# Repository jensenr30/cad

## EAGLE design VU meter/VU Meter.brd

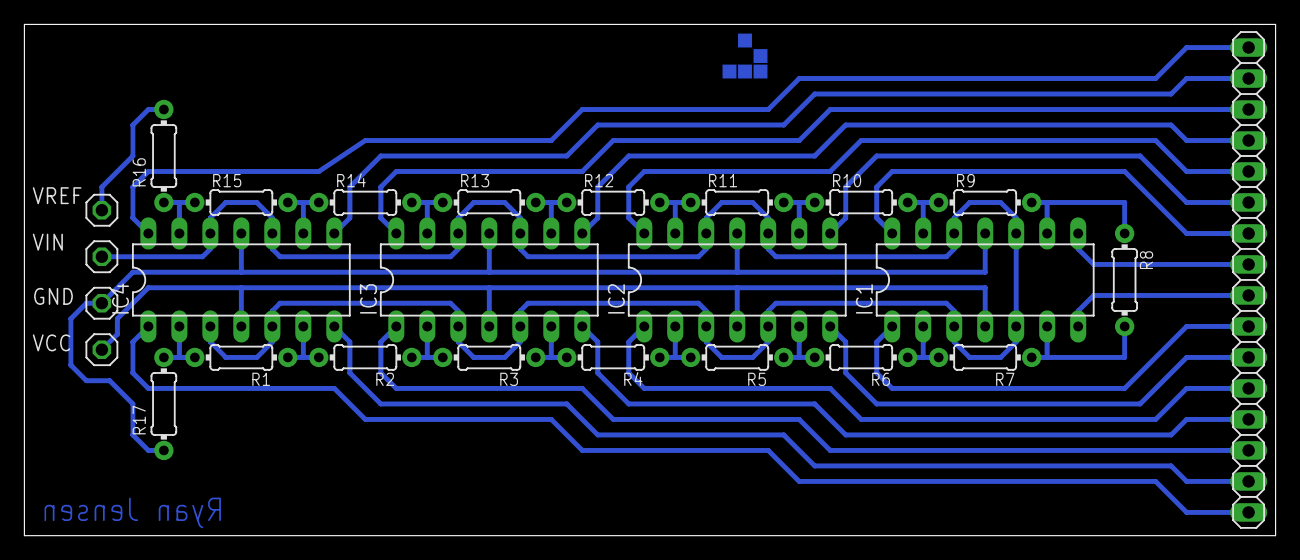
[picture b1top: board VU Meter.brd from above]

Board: 2 copper layers, 102.5 x 41.9 mm, 26 parts (0 on the bottom side), 36 nets.

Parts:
GND: 1X01
IC1, IC2, IC3, IC4: LM324N; DIL14
JP4: 1X16
R1, R2, R3, R4, R5, R6, R7, R8, R9, R10, R11, R12, R13, R14, R15, R16, R17: 10k; 0204/7
VCC: 1X01
VIN: 1X01
VREF: 1X01

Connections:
AGND: GND.1, IC1.11, IC2.11, IC3.11, IC4.11, R17.2
unnamed: IC4.9, R14.1, R15.2
unnamed: IC1.3, IC1.5, IC1.10, IC1.12, IC2.3, IC2.5, IC2.10, IC2.12, IC3.3, IC3.5, IC3.10, IC3.12, IC4.3, IC4.5, IC4.10, IC4.12, VIN.1
unnamed: IC3.13, R13.1, R14.2
unnamed: IC3.9, R12.1, R13.2
unnamed: IC2.13, R11.1, R12.2
unnamed: IC2.9, R10.1, R11.2
unnamed: IC1.13, R9.1, R10.2
unnamed: IC4.13, R15.1, R16.2
unnamed: IC4.2, R1.2, R17.1
unnamed: IC4.6, R1.1, R2.2
unnamed: IC3.2, R2.1, R3.2
unnamed: IC3.6, R3.1, R4.2
unnamed: IC2.2, R4.1, R5.2
unnamed: IC2.6, R5.1, R6.2
unnamed: IC1.2, R6.1, R7.2
unnamed: IC1.6, R7.1, R8.2
unnamed: IC1.9, R8.1, R9.2
unnamed: R16.1, VREF.1
unnamed: IC4.14, JP4.1
unnamed: IC4.8, JP4.2
unnamed: IC3.14, JP4.3
unnamed: IC3.8, JP4.4
unnamed: IC2.14, JP4.5
unnamed: IC2.8, JP4.6
unnamed: IC1.14, JP4.7
unnamed: IC1.8, JP4.8
unnamed: IC1.7, JP4.9
unnamed: IC1.1, JP4.10
unnamed: IC2.7, JP4.11
unnamed: IC4.1, JP4.16
unnamed: IC4.7, JP4.15
unnamed: IC3.1, JP4.14
unnamed: IC3.7, JP4.13
unnamed: IC2.1, JP4.12
V+: IC1.4, IC2.4, IC3.4, IC4.4
